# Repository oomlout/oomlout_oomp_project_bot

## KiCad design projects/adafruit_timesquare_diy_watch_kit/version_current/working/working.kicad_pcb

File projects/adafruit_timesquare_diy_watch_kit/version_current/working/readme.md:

# OOMP Project  
## TIMESQUARE-DIY-Watch-Kit  by adafruit  
  
oomp key: oomp_projects_flat_adafruit_timesquare_diy_watch_kit  
(snippet of original readme)  
  
- PCB for the Adafruit TIMESQUARE DIY Watch Kit   
  
<a href="http://www.adafruit.com/products/1106"><br/>Click here to purchase one from the Adafruit shop</a>  
  
__Format is EagleCAD schematic and board layout__  
  
Show up stylish AND on time to any event with this awesome looking DIY watch. We have a few watch kits here at Adafruit but we finally have one that looks good and fits well, even for ladies and kids and others with smaller wrists and hands. Its got an 8x8 bit matrix display and a repurposed silicone watch band for a professional look.  
  
64 LEDs light up to tell you the time in a variety of ways. Built into the kit are 3 different watch 'faces' - a scrolling marquee with time and date, a binary watch display (for geeks, robots, and binary fans), and a moon phase display (for beach-combers, werewolves). There's also a built-in battery meter so you can check your battery life. [Want to make your own watch? Easy! The microcontroller is an Arduino-compatible, all you need is an FTDI Friend and the Arduino IDE and you can design your own watch faces and upload them to the TIMESQUARE.](http://learn.adafruit.com/timesquare-watch-kit/uploading-new-firmware)  
  
Engineered for greatness by PaintYourDragon, this watch squeezes 500-1000 full time displays out of a coin battery, and up to one year 'resting' lifetime, so you can use this as a day-to-day timekeeper.  
  
This watch comes with an ultra bright red LED matrix and a black silicon  
  full source readme at [readme_src.md](readme_src.md)  
  
source repo at: [https://github.com/adafruit/TIMESQUARE-DIY-Watch-Kit](https://github.com/adafruit/TIMESQUARE-DIY-Watch-Kit)  
## Board  

## Schematic  

[schematic pdf](working_schematic.pdf)  
## Images

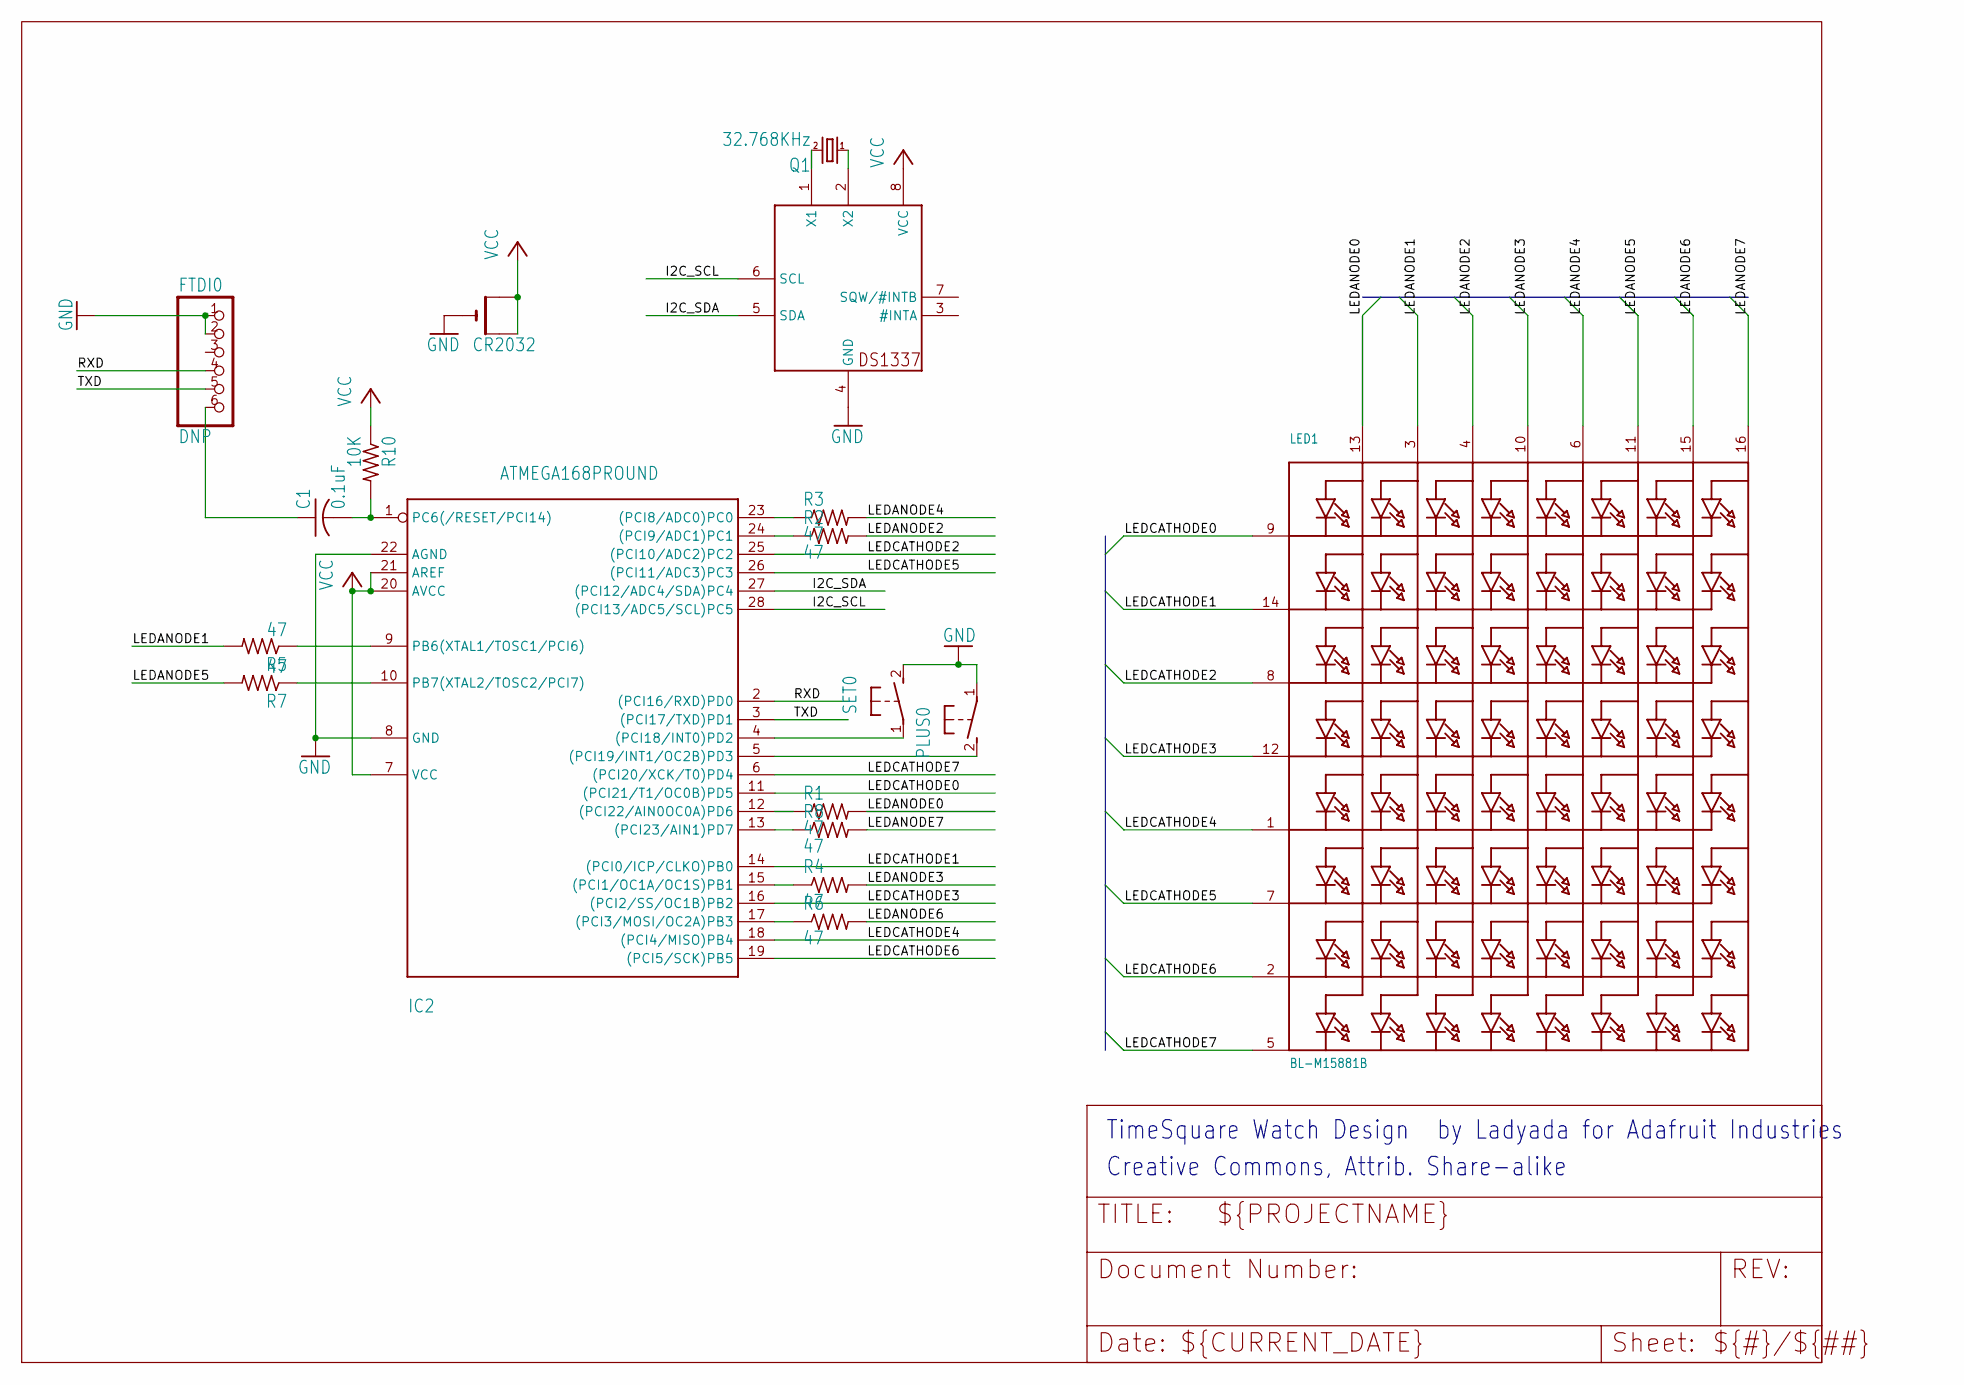
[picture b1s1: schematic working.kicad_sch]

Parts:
BATT0: CR2032; CR2032-THRU
C1: 0.1uF; C025-025X050
FTDI0: DNP; 1X06-CLEAN
IC1: DS1337; DIL08-ROUND
IC2: ATMEGA168PROUND; DIL28-3-ROUND
LED1: BL-M15881B; SEGMENT_BL-M15A881
PLUS0: 31-XXSKINNY; B3F-31XX-SKINNIER
Q1: 32.768KHz; TC38H
R1, R2, R3, R4, R5, R6, R7, R8: 47; 0204_7
R10: 10K; 0204_7
SET0: 31-XXSKINNY; B3F-31XX-SKINNIER

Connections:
GND: BATT0.-, FTDI0.1, FTDI0.2, IC1.4 (GND), IC2.8 (GND), IC2.22 (AGND), PLUS0.1, SET0.2 (S)
I2C_SCL: IC1.6 (SCL), IC2.28 ((PCI13/ADC5/SCL)PC5)
I2C_SDA: IC1.5 (SDA), IC2.27 ((PCI12/ADC4/SDA)PC4)
LEDANODE0: LED1.13 (A1), R1.2
LEDANODE1: LED1.3 (A2), R5.2
LEDANODE2: LED1.4 (A3), R2.2
LEDANODE3: LED1.10 (A4), R4.2
LEDANODE4: LED1.6 (A5), R3.2
LEDANODE5: LED1.11 (A6), R7.2
LEDANODE6: LED1.15 (A7), R6.2
LEDANODE7: LED1.16 (A8), R8.2
LEDCATHODE0: IC2.11 ((PCI21/T1/OC0B)PD5), LED1.9 (K1)
LEDCATHODE1: IC2.14 ((PCI0/ICP/CLKO)PB0), LED1.14 (K2)
LEDCATHODE2: IC2.25 ((PCI10/ADC2)PC2), LED1.8 (K3)
LEDCATHODE3: IC2.16 ((PCI2/SS/OC1B)PB2), LED1.12 (K4)
LEDCATHODE4: IC2.18 ((PCI4/MISO)PB4), LED1.1 (K5)
LEDCATHODE5: IC2.26 ((PCI11/ADC3)PC3), LED1.7 (K6)
LEDCATHODE6: IC2.19 ((PCI5/SCK)PB5), LED1.2 (K7)
LEDCATHODE7: IC2.6 ((PCI20/XCK/T0)PD4), LED1.5 (K8)
unnamed: C1.2, IC2.1 (PC6(/RESET/PCI14)), R10.2
unnamed: IC1.1 (X1), Q1.2
unnamed: IC1.2 (X2), Q1.1
unnamed: IC2.4 ((PCI18/INT0)PD2), SET0.1
unnamed: IC2.5 ((PCI19/INT1/OC2B)PD3), PLUS0.2 (S)
unnamed: IC2.12 ((PCI22/AIN0OC0A)PD6), R1.1
unnamed: IC2.23 ((PCI8/ADC0)PC0), R3.1
unnamed: IC2.9 (PB6(XTAL1/TOSC1/PCI6)), R5.1
unnamed: IC2.10 (PB7(XTAL2/TOSC2/PCI7)), R7.1
unnamed: IC2.24 ((PCI9/ADC1)PC1), R2.1
unnamed: IC2.17 ((PCI3/MOSI/OC2A)PB3), R6.1
unnamed: IC2.13 ((PCI23/AIN1)PD7), R8.1
unnamed: IC2.15 ((PCI1/OC1A/OC1S)PB1), R4.1
unnamed: C1.1, FTDI0.6
RXD: FTDI0.4, IC2.2 ((PCI16/RXD)PD0)
TXD: FTDI0.5, IC2.3 ((PCI17/TXD)PD1)
VCC: BATT0.+1 (+), BATT0.+2 (+1), IC1.8 (VCC), IC2.7 (VCC), IC2.20 (AVCC), IC2.21 (AREF), R10.1

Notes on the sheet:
Creative Commons, Attrib. Share-alike
by Ladyada for Adafruit Industries
TimeSquare Watch Design

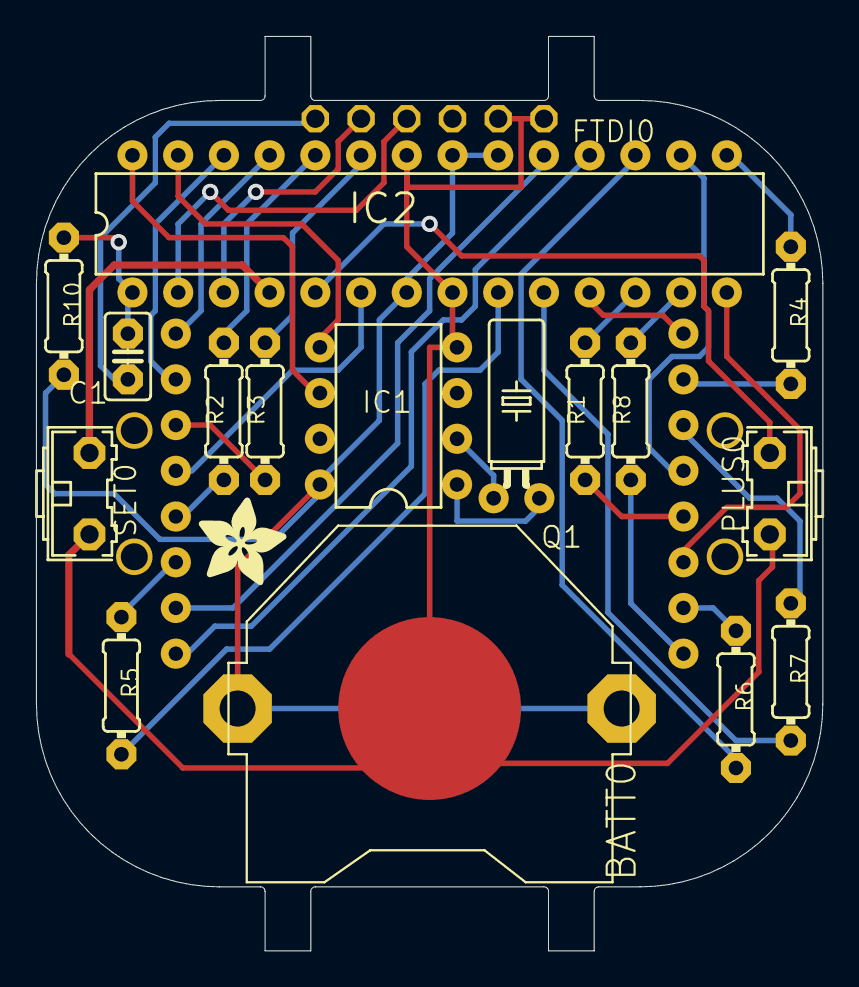
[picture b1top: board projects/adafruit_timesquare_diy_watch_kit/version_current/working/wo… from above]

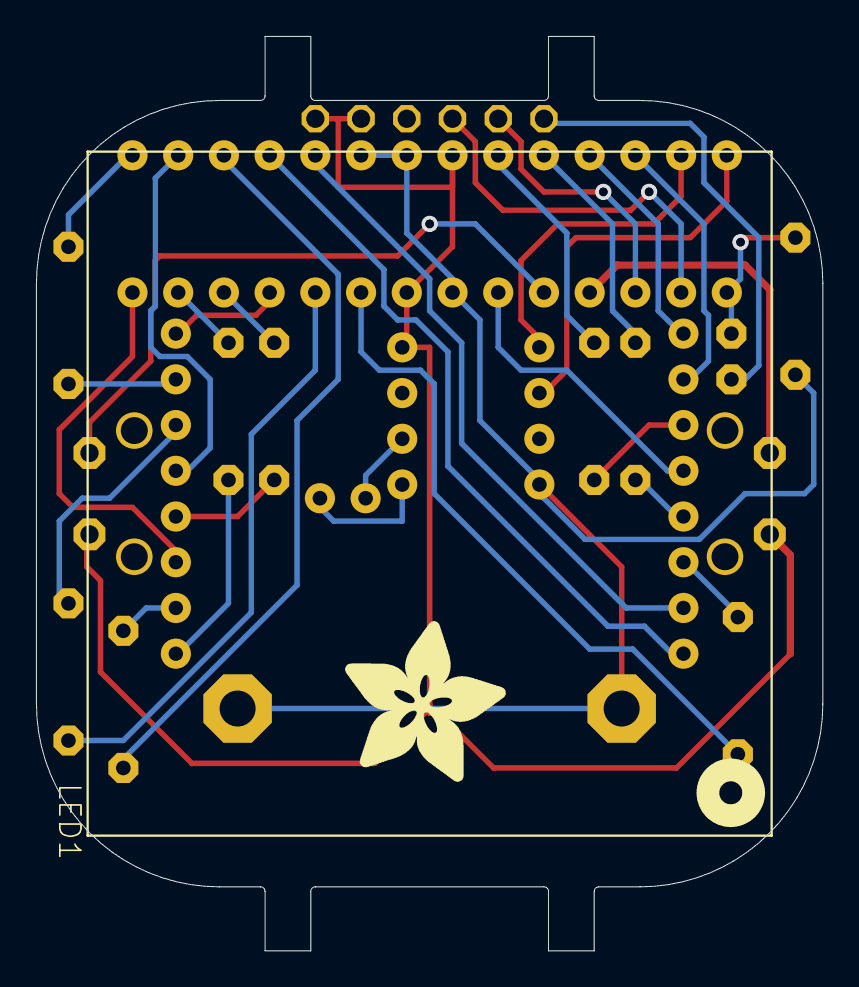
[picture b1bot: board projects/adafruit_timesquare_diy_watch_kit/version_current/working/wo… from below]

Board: 16 copper layers, 43.7 x 50.8 mm, 20 parts (2 on the bottom side), 36 nets.

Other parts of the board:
U$1: ADAFRUIT_5MM
U$2: ADAFRUIT_9MM

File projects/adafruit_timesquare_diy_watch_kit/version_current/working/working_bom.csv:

Row,Description,Part,References,Value,Footprint,Quantity Per PCB,Status,Datasheet
1,,CR2032THM,BATT0,CR2032,CR2032-THRU,1, ,
2,,C-US025-025X050,C1,0.1uF,C025-025X050,1, ,
3,,ATMEGA168PROUND,IC2,ATMEGA168PROUND,DIL28-3-ROUND,1, ,
4,,DS1337,IC1,DS1337,DIL08-ROUND,1, ,
5,,SEGMENT_8X8_ROWCATHODEBL-M15,LED1,BL-M15881B,SEGMENT_BL-M15A881,1, ,
6,,31-XXSKINNY,PLUS0 SET0,31-XXSKINNY,B3F-31XX-SKINNIER,2, ,
7,,CRYSTALTC38H,Q1,32.768KHz,TC38H,1, ,
8,,R-US_0204/7,R1 R2 R3 R4 R5 R6 R7 R8,47,0204_7,8, ,
9,,R-US_0204/7,R10,10K,0204_7,1, ,





Project info:
Schematic:,working
Variant:,default
Revision:,
Date:,2023-08-03_17-21-23
KiCad Version:,7.0.6-7.0.6~ubuntu22.04.1
Statistics:
Component Groups:,10
Component Count:,18 (0 SMD/ 0 THT)
Fitted Components:,17 (0 SMD/ 0 THT)
Number of PCBs:,1
Total Components:,17

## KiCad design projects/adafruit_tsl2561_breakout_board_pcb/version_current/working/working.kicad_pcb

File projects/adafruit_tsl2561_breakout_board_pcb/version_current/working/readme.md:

# TSL2561-breakout-board-PCB by adafruit  
This is a harvested standardized copy of a project from github.  
The original project can be found at:  
https://github.com/adafruit/TSL2561-breakout-board-PCB  
Please consult that link for additional, details, files, and license information.  
Note: It was auto harvested and if the original repo had more than one board file or anything out of the ordinary the files here are likely not representative.

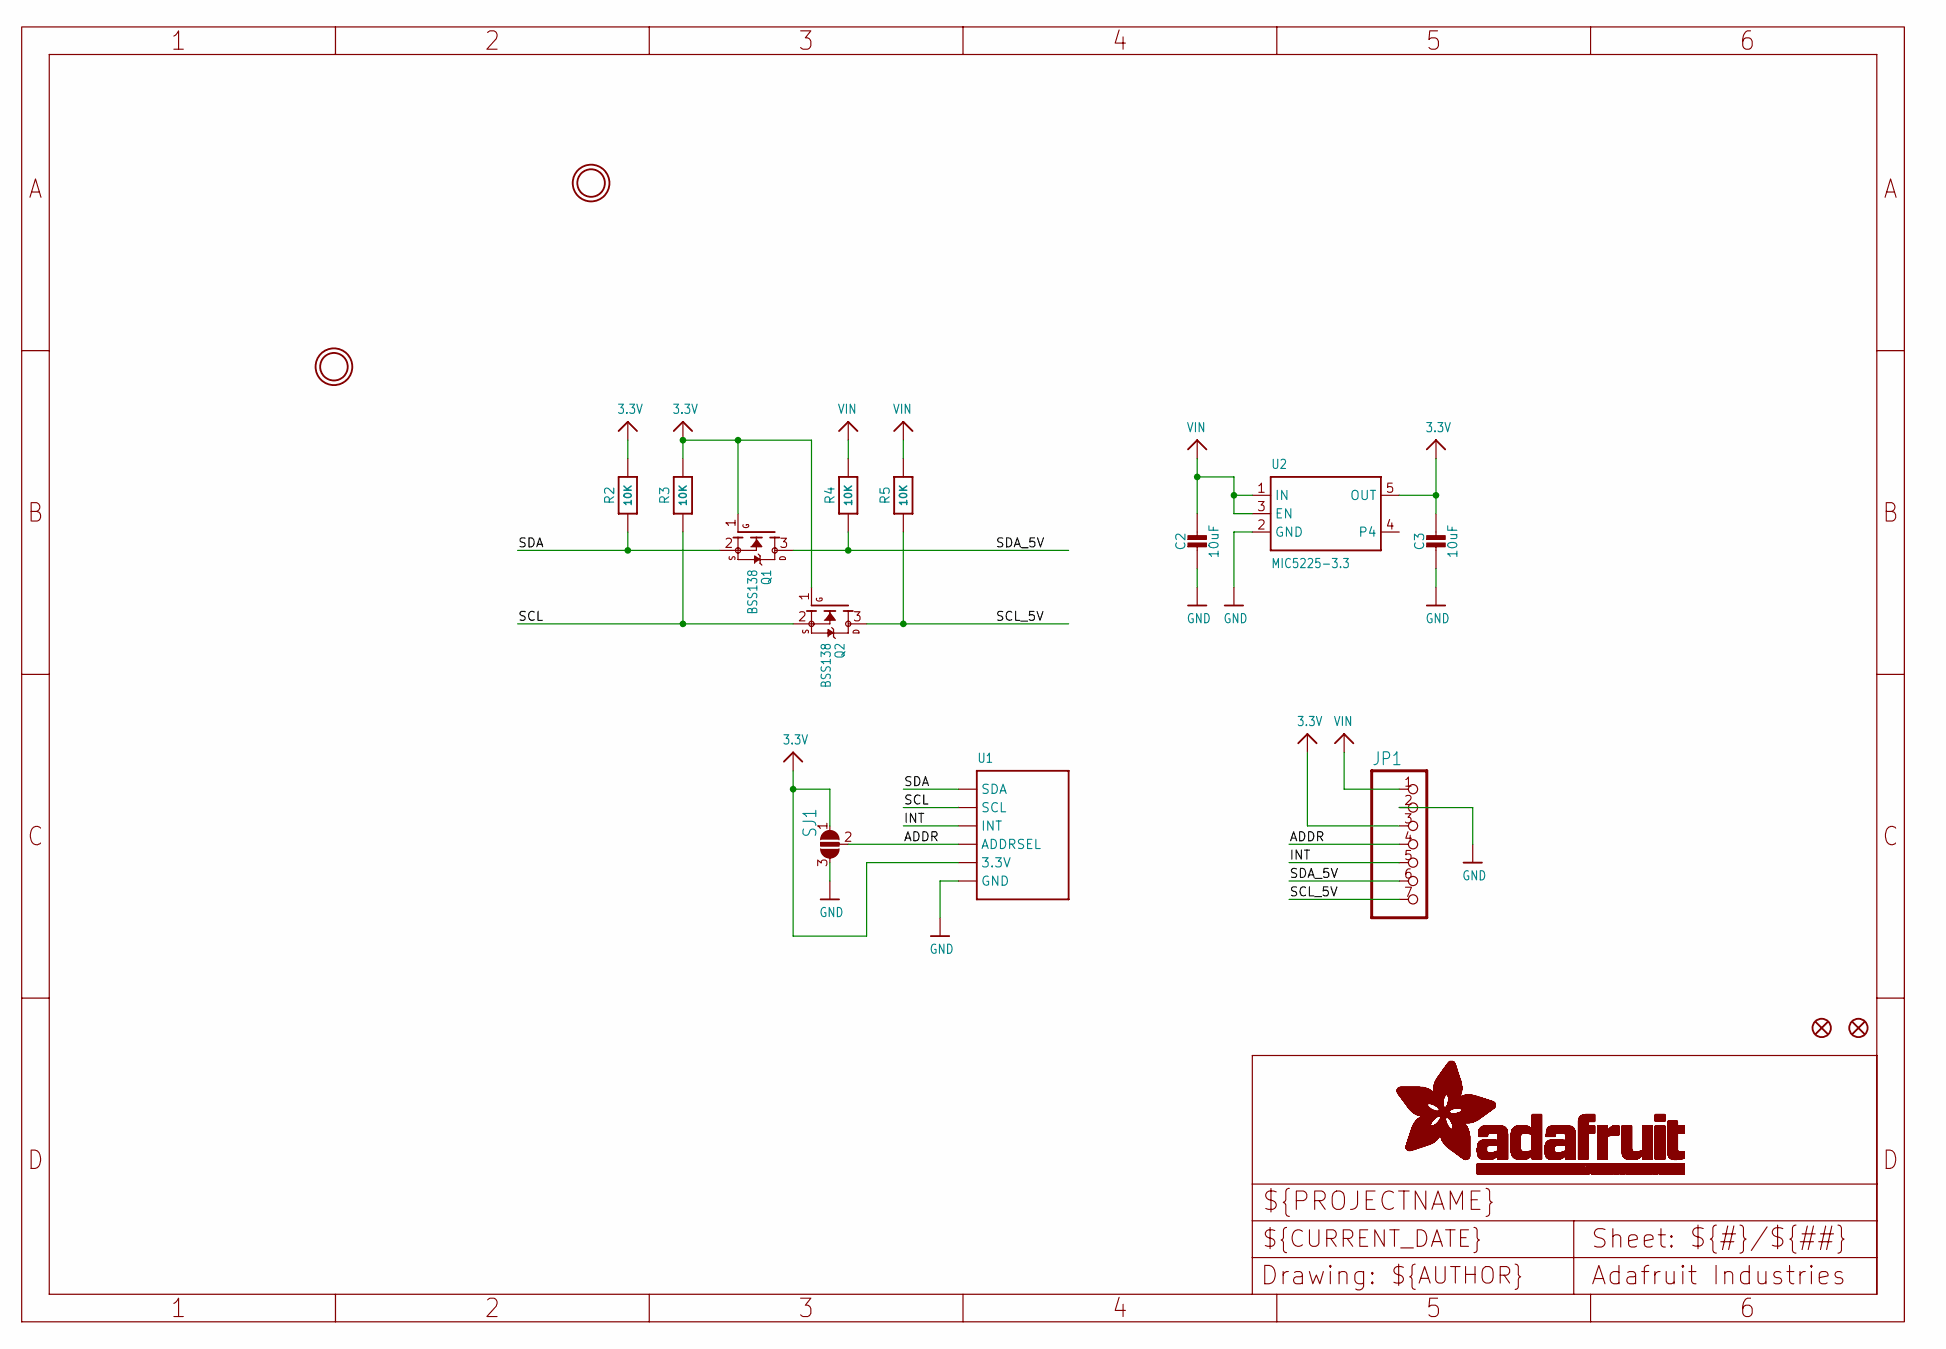
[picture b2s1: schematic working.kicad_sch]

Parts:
C2, C3: 10uF; 0805-NO
FID1, FID2: FIDUCIAL""; FIDUCIAL_1MM
JP1: HEADER-1X7THICKER; 1X07_ROUND_76
Q1, Q2: BSS138; SOT23-WIDE
R2, R3, R4, R5: 10K; 0805-NO
SJ1: SOLDERJUMPER_2WAY; SOLDERJUMPER_2WAY_OPEN_NOPASTE
U1: LIGHT_TSL2561; TSL2561_FN
U2: MIC5225-3.3; SOT23-5
U$18, U$19: MOUNTINGHOLE2.5; MOUNTINGHOLE_2.5_PLATED

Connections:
3.3V: C3.1, JP1.3, Q1.1 (G), Q2.1 (G), R2.2, R3.2, SJ1.1, U1.VDD (3.3V), U2.5 (OUT)
ADDR: JP1.4, SJ1.2, U1.ADR (ADDRSEL)
GND: C2.2, C3.2, JP1.2, SJ1.3, U1.VSS (GND), U2.2 (GND)
INT: JP1.5, U1.INT
SCL: Q2.2 (S), R3.1, U1.CLK (SCL)
SCL_5V: JP1.7, Q2.3 (D), R5.1
SDA: Q1.2 (S), R2.1, U1.DATA (SDA)
SDA_5V: JP1.6, Q1.3 (D), R4.1
VIN: C2.1, JP1.1, R4.2, R5.2, U2.1 (IN), U2.3 (EN)

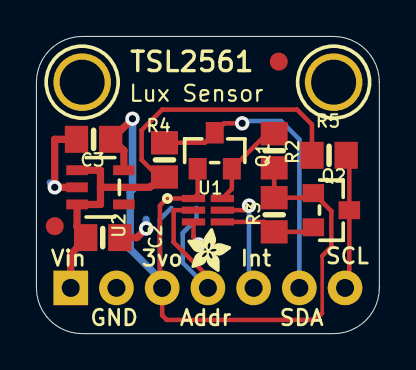
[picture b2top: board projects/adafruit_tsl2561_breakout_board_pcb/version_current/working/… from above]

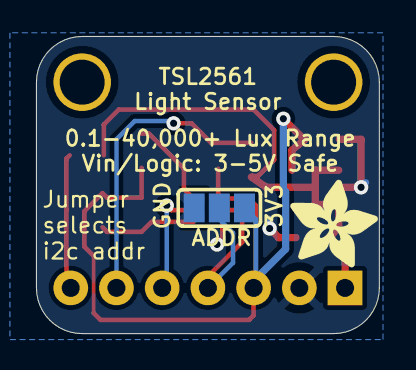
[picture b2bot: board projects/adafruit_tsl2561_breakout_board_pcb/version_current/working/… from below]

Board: 2 copper layers, 19.1 x 16.5 mm, 18 parts (2 on the bottom side), 9 nets.

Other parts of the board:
U$15: ADAFRUIT_2.5MM
U$20: ADAFRUIT_5MM

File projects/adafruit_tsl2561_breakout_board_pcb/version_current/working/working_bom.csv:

Row,Description,Part,References,Value,Footprint,Quantity Per PCB,Status,Datasheet
1,,CAP_CERAMIC0805-NOOUTLINE,C2 C3,10uF,0805-NO,2, ,
2,,HEADER-1X7THICKER,JP1,HEADER-1X7THICKER,1X07_ROUND_76,1, ,
3,,MOSFET-NWIDE,Q1 Q2,BSS138,SOT23-WIDE,2, ,
4,,RESISTOR0805_NOOUTLINE,R2 R3 R4 R5,10K,0805-NO,4, ,
5,,LIGHT_TSL2561,U1,LIGHT_TSL2561,TSL2561_FN,1, ,
6,,VREG_SOT23-5,U2,MIC5225-3.3,SOT23-5,1, ,





Project info:
Schematic:,working
Variant:,default
Revision:,
Date:,2023-08-03_17-21-23
KiCad Version:,7.0.6-7.0.6~ubuntu22.04.1
Statistics:
Component Groups:,6
Component Count:,11 (0 SMD/ 0 THT)
Fitted Components:,11 (0 SMD/ 0 THT)
Number of PCBs:,1
Total Components:,11

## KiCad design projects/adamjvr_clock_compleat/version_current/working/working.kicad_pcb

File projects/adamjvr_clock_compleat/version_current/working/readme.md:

# OOMP Project  
## Clock-Compleat  by adamjvr  
  
oomp key: oomp_projects_flat_adamjvr_clock_compleat  
(snippet of original readme)  

  full source readme at [readme_src.md](readme_src.md)  
  
source repo at: [https://github.com/adamjvr/Clock-Compleat](https://github.com/adamjvr/Clock-Compleat)  
## Board  

## Schematic  

[schematic pdf](working_schematic.pdf)  
## Images

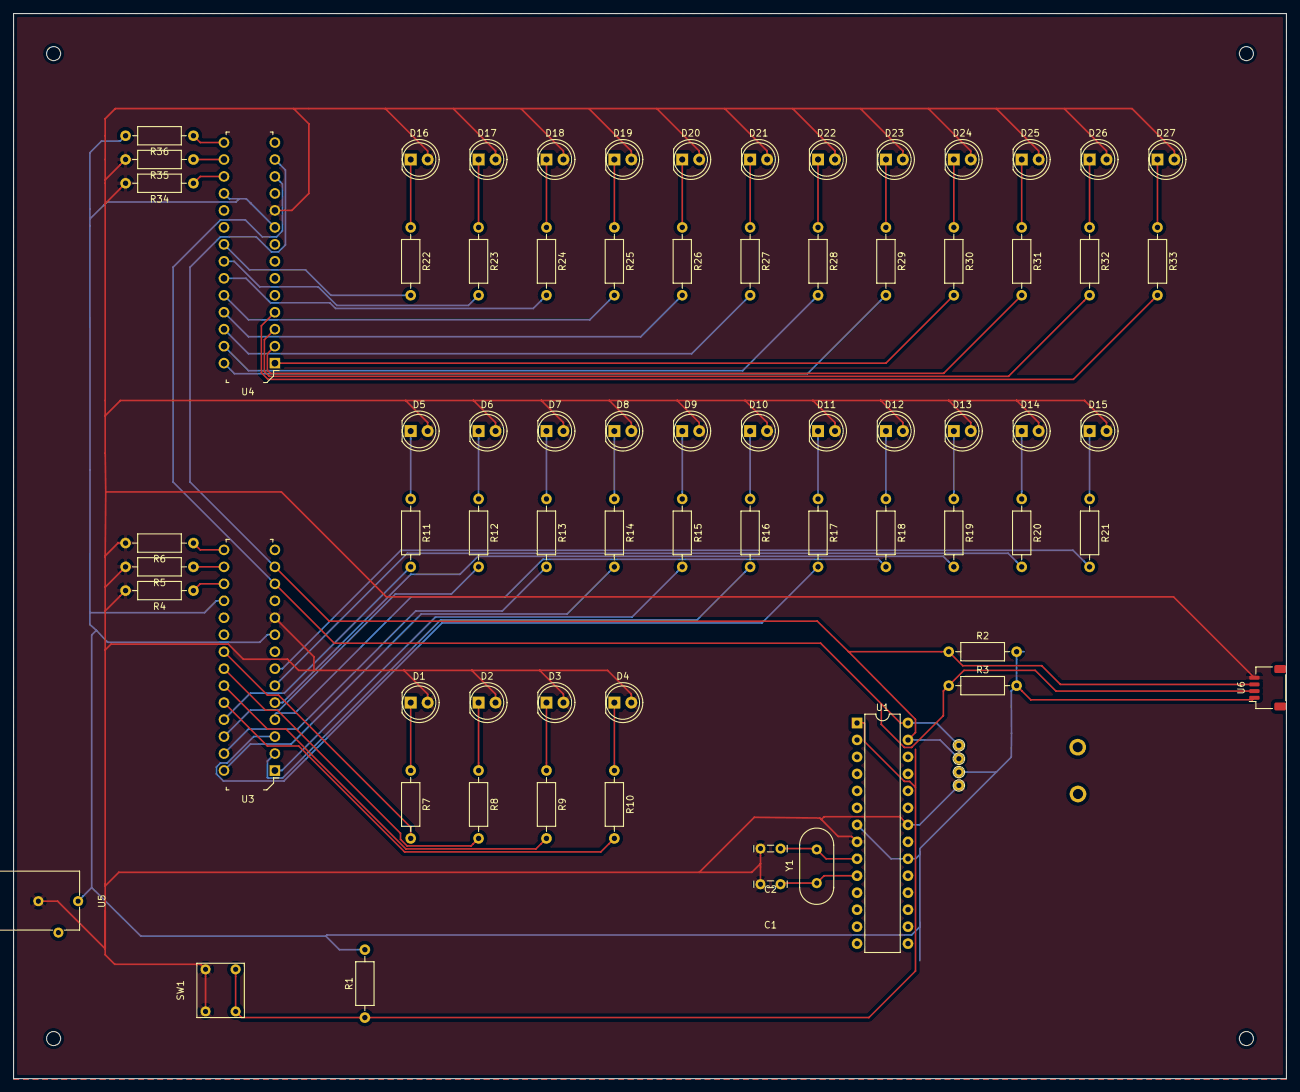
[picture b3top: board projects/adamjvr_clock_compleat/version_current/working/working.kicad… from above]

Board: 2 copper layers, 190.5 x 159.4 mm, 73 parts (0 on the bottom side), 67 nets.

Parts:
C1, C2: Capacitor
D1, D2, D3, D4, D5, D6, D7, D8, D9, D10, D11, D12, D13, D14, D15, D16, D17, D18, D19, D20, D21, D22, D23, D24, D25, D26, D27: Blue; LED_D5.0mm
R1, R4, R5, R6, R7, R8, R9, R10, R11, R12, R13, R14, R15, R16, R17, R18, R19, R20, R21, R22, R23, R24, R25, R26, R27, R28, R29, R30, R31, R32, R33, R34, R35, R36: 1k; R_Axial_DIN0207_L6.3mm_D2.5mm_P10.16mm_Horizontal
R2, R3: 4.7k; R_Axial_DIN0207_L6.3mm_D2.5mm_P10.16mm_Horizontal
SW1: SW_Push_Dual; Pushbutton
U1: ATmega328P-PU; DIP-28_W7.62mm
U2: DS3231MZ; DS3231
U3, U4: MCP23017-E_SP; DIP-28_W7.62mm
U5: Barreljack; BarrelJack
U6: JST4pin; JST_SH_SM04B-SRSS-TB_1x04-1MP_P1.00mm_Horizontal
Y1: Crystal

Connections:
+5V: R1.2, R2.2, R3.2, R36.2, U1.7, U1.20, U2.2, U3.9, U3.18, U4.9, U4.18, U5.1, U6.1
/clock minute/SCL: R3.1, U1.28, U2.8, U3.12, U4.12, U6.2
/clock minute/SDA: R2.1, U1.27, U2.7, U3.13, U4.13, U6.3
GND: C1.2, C2.2, D1.2, D2.2, D3.2, D4.2, D5.2, D6.2, D7.2, D8.2, D9.2, D10.2, D11.2, D12.2, D13.2, D14.2, D15.2, D16.2, D17.2, D18.2, D19.2, D20.2, D21.2, D22.2, D23.2, D24.2, D25.2, D26.2, D27.2, R4.2, R5.2, R6.2, R34.2, R35.2, SW1.2, SW1.4, U1.8, U1.22, U2.5, U3.10, U4.10, U5.2, U6.4
GPB0: R15.2, U3.1
GPB1: R16.2, U3.2
GPB2: R17.2, U3.3
GPB3: R18.2, U3.4
GPB4: R19.2, U3.5
GPB5: R20.2, U3.6
GPB6: R21.2, U3.7
HGPB0: R30.2, U4.1
HGPB1: R31.2, U4.2
HGPB2: R32.2, U4.3
HGPB3: R33.2, U4.4
unnamed: C1.1, U1.10, Y1.1
unnamed: C2.1, U1.9, Y1.2
unnamed: D1.1, R7.1
unnamed: D2.1, R8.1
unnamed: D3.1, R9.1
unnamed: D4.1, R10.1
unnamed: D5.1, R11.1
unnamed: D6.1, R12.1
unnamed: D7.1, R13.1
unnamed: D8.1, R14.1
unnamed: D9.1, R15.1
unnamed: D10.1, R16.1
unnamed: D11.1, R17.1
unnamed: D12.1, R18.1
unnamed: D13.1, R19.1
unnamed: D14.1, R20.1
unnamed: D15.1, R21.1
unnamed: D16.1, R22.1
unnamed: D17.1, R23.1
unnamed: D18.1, R24.1
unnamed: D19.1, R25.1
unnamed: D20.1, R26.1
unnamed: D21.1, R27.1
unnamed: D22.1, R28.1
unnamed: D23.1, R29.1
unnamed: D24.1, R30.1
unnamed: D25.1, R31.1
unnamed: D26.1, R32.1
unnamed: D27.1, R33.1
unnamed: R1.1, SW1.1, SW1.3, U1.1
unnamed: R4.1, U3.17
unnamed: R5.1, U3.16
unnamed: R6.1, U3.15
unnamed: R7.2, U3.21
unnamed: R8.2, U3.22
unnamed: R9.2, U3.23
unnamed: R10.2, U3.24
unnamed: R11.2, U3.25
unnamed: R12.2, U3.26
unnamed: R13.2, U3.27
unnamed: R14.2, U3.28
unnamed: R22.2, U4.21
unnamed: R23.2, U4.22
unnamed: R24.2, U4.23
unnamed: R25.2, U4.24
unnamed: R26.2, U4.25
unnamed: R27.2, U4.26
unnamed: R28.2, U4.27
unnamed: R29.2, U4.28
unnamed: R34.1, U4.17
unnamed: R35.1, U4.16
unnamed: R36.1, U4.15

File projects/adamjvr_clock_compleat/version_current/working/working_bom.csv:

"Id";"Designator";"Footprint";"Quantity";"Designation";"Supplier and ref";
1;"U6";"JST_SH_SM04B-SRSS-TB_1x04-1MP_P1.00mm_Horizontal";1;"JST4pin";;;
2;"U2";"DS3231";1;"DS3231MZ";;;
3;"U1";"DIP-28_W7.62mm";1;"ATmega328P-PU";;;
4;"U5";"BarrelJack";1;"Barreljack";;;
5;"R36,R35,R34,R33,R32,R31,R30,R29,R28,R27,R26,R25,R24,R23,R22,R21,R20,R19,R18,R17,R16,R15,R14,R13,R12,R11,R10,R9,R8,R7,R6,R5,R4,R1";"R_Axial_DIN0207_L6.3mm_D2.5mm_P10.16mm_Horizontal";34;"1k";;;
6;"Y1";"Crystal";1;"Crystal";;;
7;"U4,U3";"DIP-28_W7.62mm";2;"MCP23017-E_SP";;;
8;"SW1";"Pushbutton";1;"SW_Push_Dual";;;
9;"R3,R2";"R_Axial_DIN0207_L6.3mm_D2.5mm_P10.16mm_Horizontal";2;"4.7k";;;
10;"D27,D26,D25,D24,D23,D22,D21,D20,D19,D18,D17,D16,D15,D14,D13,D12,D11,D10,D9,D8,D7,D6,D5,D4,D3,D2,D1";"LED_D5.0mm";27;"Blue";;;
11;"C2,C1";"Capacitor";2;"Capacitor";;;

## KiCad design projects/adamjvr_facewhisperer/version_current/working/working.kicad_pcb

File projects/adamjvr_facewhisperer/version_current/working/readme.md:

# facewhisperer by adamjvr  
This is a harvested standardized copy of a project from github.  
The original project can be found at:  
https://github.com/adamjvr/facewhisperer  
Please consult that link for additional, details, files, and license information.  
Note: It was auto harvested and if the original repo had more than one board file or anything out of the ordinary the files here are likely not representative.

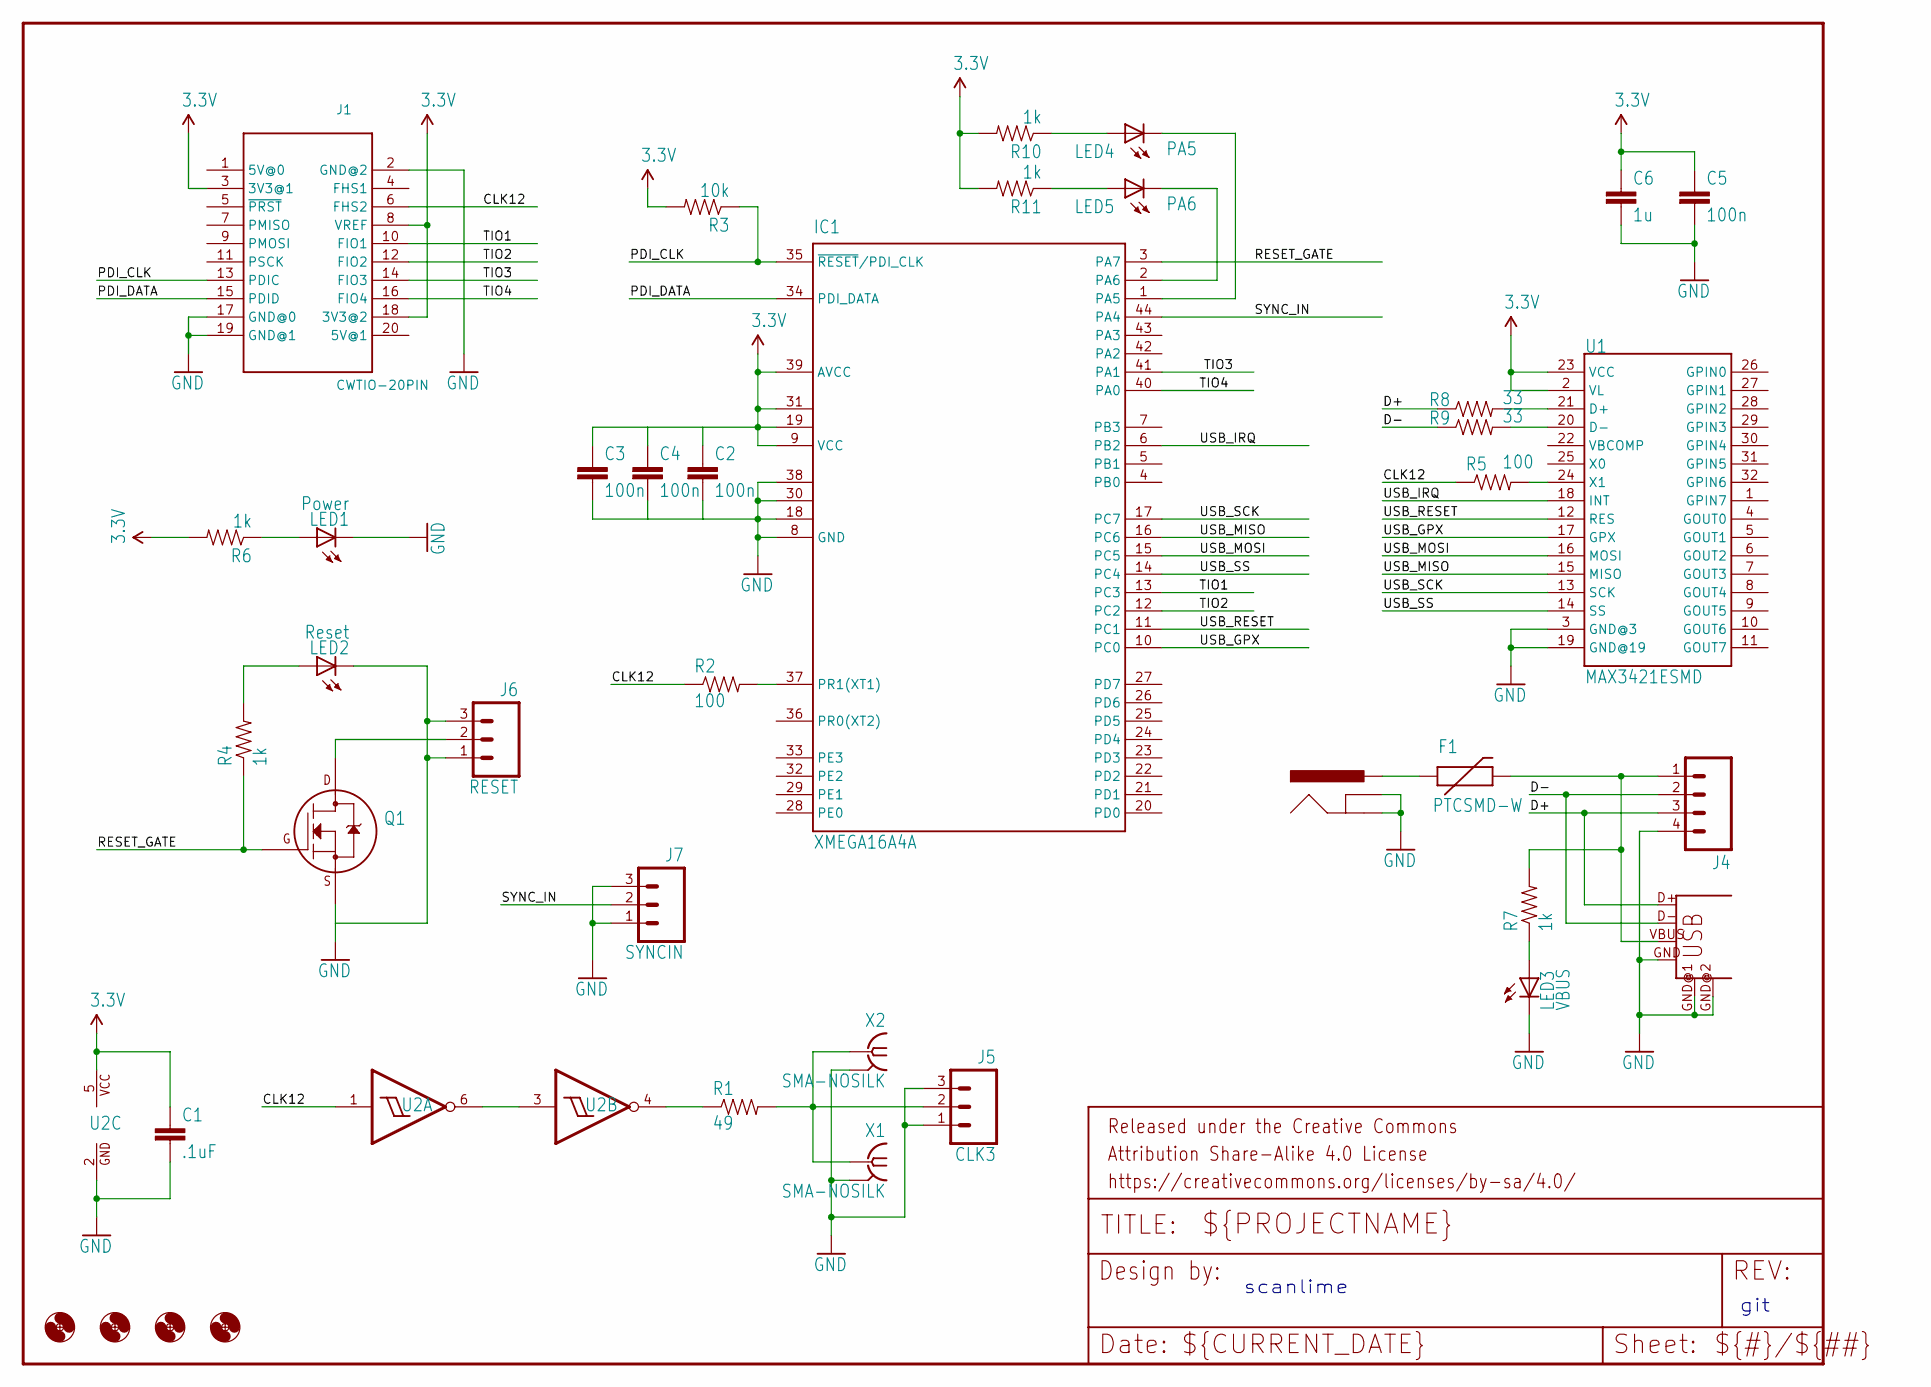
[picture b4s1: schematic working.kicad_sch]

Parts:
C1: .1uF; 0805
C2, C3, C4, C5: 100n; 0805
C6: 1u; 0805
F1: PTCSMD-W; PTC-1206-WIDE
FRAME1: FRAME-LETTERNO_PACKAGE; DUMMY
H1, H2, H3, H4: MOUNT-HOLE3.2; 3,2
IC1: XMEGA16A4A; TQFP44
J1: CWTIO-20PIN; PINSHRD_PTH_2X10
J2: POWER_JACKPTH; POWER_JACK_PTH
J3: USB-A-H
J4: M04LOCK_LONGPADS; 1X04_LOCK_LONGPADS
J5: CLK3; 1X03_LOCK_LONGPADS
J6: RESET; 1X03_LOCK_LONGPADS
J7: SYNCIN; 1X03_LOCK_LONGPADS
LED1: Power; 1206
LED2: Reset; 1206
LED3: VBUS; 1206
LED4: PA5; 1206
LED5: PA6; 1206
Q1: 2N700_SOT23; SOT-23
R1: 49; 0805
R2, R5: 100; 0805
R3: 10k; 0805
R4, R6, R7, R10, R11: 1k; 0805
R8, R9: 33; 0805
U1: MAX3421ESMD; TQFP32-5MM-MILLABLE
U2: NC7WZ14; SC70-6-MILLABLE
X1, X2: SMA-NOSILK; J502-ND-142-0711-821_826-NOSILK

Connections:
3.3V: C1.1, C2.1, C3.1, C4.1, C5.1, C6.1, IC1.9 (VCC), IC1.19 (VCC1), IC1.31 (VCC2), IC1.39 (AVCC), J1.3 (3V3@1), J1.8 (VREF), J1.18 (3V3@2), R3.2, R6.2, R10.2, R11.2, U1.2 (VL), U1.23 (VCC), U2.5 (VCC)
CLK12: J1.6 (FHS2), R2.1, R5.1, U2.1 (IN)
D+: J3.D+, J4.3, R8.1
D-: J3.D-, J4.2, R9.1
GND: C1.2, C2.2, C3.2, C4.2, C5.2, C6.2, IC1.8 (GND), IC1.18 (GND1), IC1.30 (GND2), IC1.38 (GND3), J1.2 (GND@2), J1.17 (GND@0), J1.19 (GND@1), J2.GND, J2.GNDBREAK, J3.GND, J3.GND@1, J3.GND@2, J4.4, J5.1, J5.3, J6.1, J6.3, J7.1, J7.3, LED1.C, LED2.C, LED3.C, Q1.2 (S), U1.3 (GND@3), U1.19 (GND@19), U2.2 (GND), X1.G@1 (2), X1.G@2 (2), X1.G@3 (2), X1.G@4 (2), X2.G@1 (2), X2.G@2 (2), X2.G@3 (2), X2.G@4 (2)
unnamed: U2.3 (IN), U2.6 (OUT)
unnamed: R1.1, U2.4 (OUT)
unnamed: J5.2, R1.2, X1.1, X2.1
unnamed: R5.2, U1.24 (X1)
unnamed: F1.2, J3.VBUS, J4.1, R7.2
unnamed: LED2.A, R4.2
unnamed: IC1.37 (PR1(XT1)), R2.2
unnamed: J6.2, Q1.3 (D)
unnamed: LED1.A, R6.1
unnamed: LED3.A, R7.1
unnamed: R9.2, U1.20 (D-)
unnamed: R8.2, U1.21 (D+)
unnamed: F1.1, J2.PWR
unnamed: LED4.A, R10.1
unnamed: LED5.A, R11.1
unnamed: IC1.2 (PA6), LED5.C
unnamed: IC1.1 (PA5), LED4.C
PDI_CLK: IC1.35 (~RESET/PDI_CLK), J1.13 (PDIC), R3.1
PDI_DATA: IC1.34 (PDI_DATA), J1.15 (PDID)
RESET_GATE: IC1.3 (PA7), Q1.1 (G), R4.1
SYNC_IN: IC1.44 (PA4), J7.2
TIO1: IC1.13 (PC3), J1.10 (FIO1)
TIO2: IC1.12 (PC2), J1.12 (FIO2)
TIO3: IC1.41 (PA1), J1.14 (FIO3)
TIO4: IC1.40 (PA0), J1.16 (FIO4)
USB_GPX: IC1.10 (PC0), U1.17 (GPX)
USB_IRQ: IC1.6 (PB2), U1.18 (INT)
USB_MISO: IC1.16 (PC6), U1.15 (MISO)
USB_MOSI: IC1.15 (PC5), U1.16 (MOSI)
USB_RESET: IC1.11 (PC1), U1.12 (RES)
USB_SCK: IC1.17 (PC7), U1.13 (SCK)
USB_SS: IC1.14 (PC4), U1.14 (SS)

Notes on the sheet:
git
scanlime

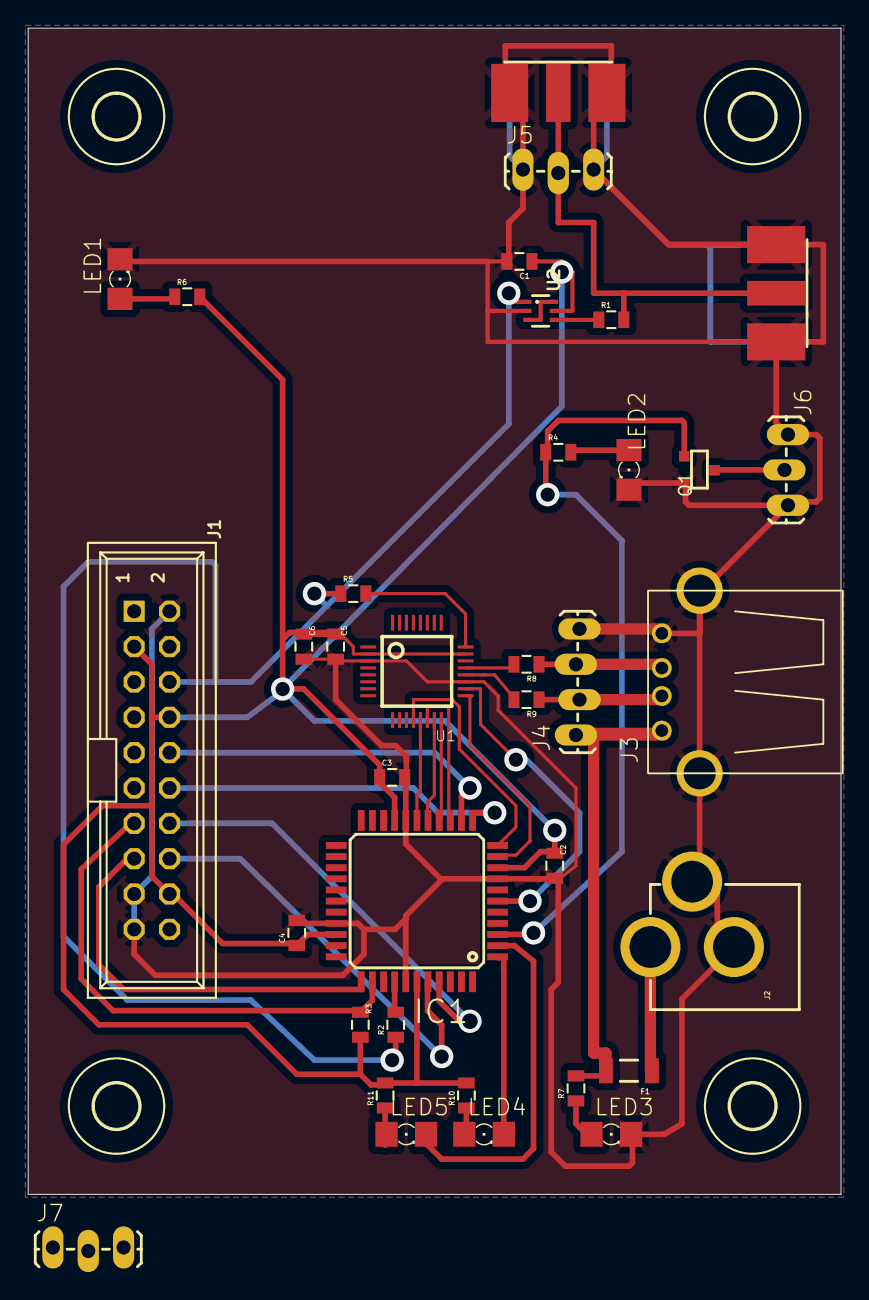
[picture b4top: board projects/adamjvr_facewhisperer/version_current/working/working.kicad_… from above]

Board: 2 copper layers, 58.4 x 83.8 mm, 41 parts (0 on the bottom side), 37 nets.

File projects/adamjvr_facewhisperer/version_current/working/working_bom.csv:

"Id";"Designator";"Footprint";"Quantity";"Designation";"Supplier and ref";
1;"X1";"J502-ND-142-0711-821_826-NOSILK";1;"CLK1";;;
2;"Q1";"SOT-23";1;"";;;
3;"LED3";"1206";1;"VBUS";;;
4;"IC1";"TQFP44";1;"XMEGA128D4";;;
5;"R2,R5";"0805";2;"100";;;
6;"J5";"1X03_LOCK_LONGPADS";1;"CLK3";;;
7;"R3";"0805";1;"10k";;;
8;"H2,H1,H4,H3";"3,2";4;"MOUNT-HOLE3.2";;;
9;"LED4";"1206";1;"PA5";;;
10;"C2,C4,C5,C3";"0805";4;"100n";;;
11;"R11,R10,R7,R6,R4";"0805";5;"1k";;;
12;"U2";"SC70-6-MILLABLE";1;"NC7WZ14";;;
13;"J7";"1X03_LOCK_LONGPADS";1;"SYNCIN";;;
14;"J3";"USB-A-H";1;"USB-A-H";;;
15;"F1";"PTC-1206-WIDE";1;"PTC 2A";;;
16;"LED1";"1206";1;"Power";;;
17;"J4";"1X04_LOCK_LONGPADS";1;"";;;
18;"LED2";"1206";1;"Reset";;;
19;"R8,R9";"0805";2;"33";;;
20;"J2";"POWER_JACK_PTH";1;"VUSB IN";;;
21;"LED5";"1206";1;"PA6";;;
22;"FRAME1";"DUMMY";1;"FRAME-LETTERNO_PACKAGE";;;
23;"C6";"0805";1;"1u";;;
24;"C1";"0805";1;".1uF";;;
25;"X2";"J502-ND-142-0711-821_826-NOSILK";1;"CLK2";;;
26;"R1";"0805";1;"49";;;
27;"U1";"TQFP32-5MM-MILLABLE";1;"MAX3421ESMD";;;
28;"J6";"1X03_LOCK_LONGPADS";1;"RESET";;;
29;"J1";"PINSHRD_PTH_2X10";1;"CWTIO-20PIN";;;
